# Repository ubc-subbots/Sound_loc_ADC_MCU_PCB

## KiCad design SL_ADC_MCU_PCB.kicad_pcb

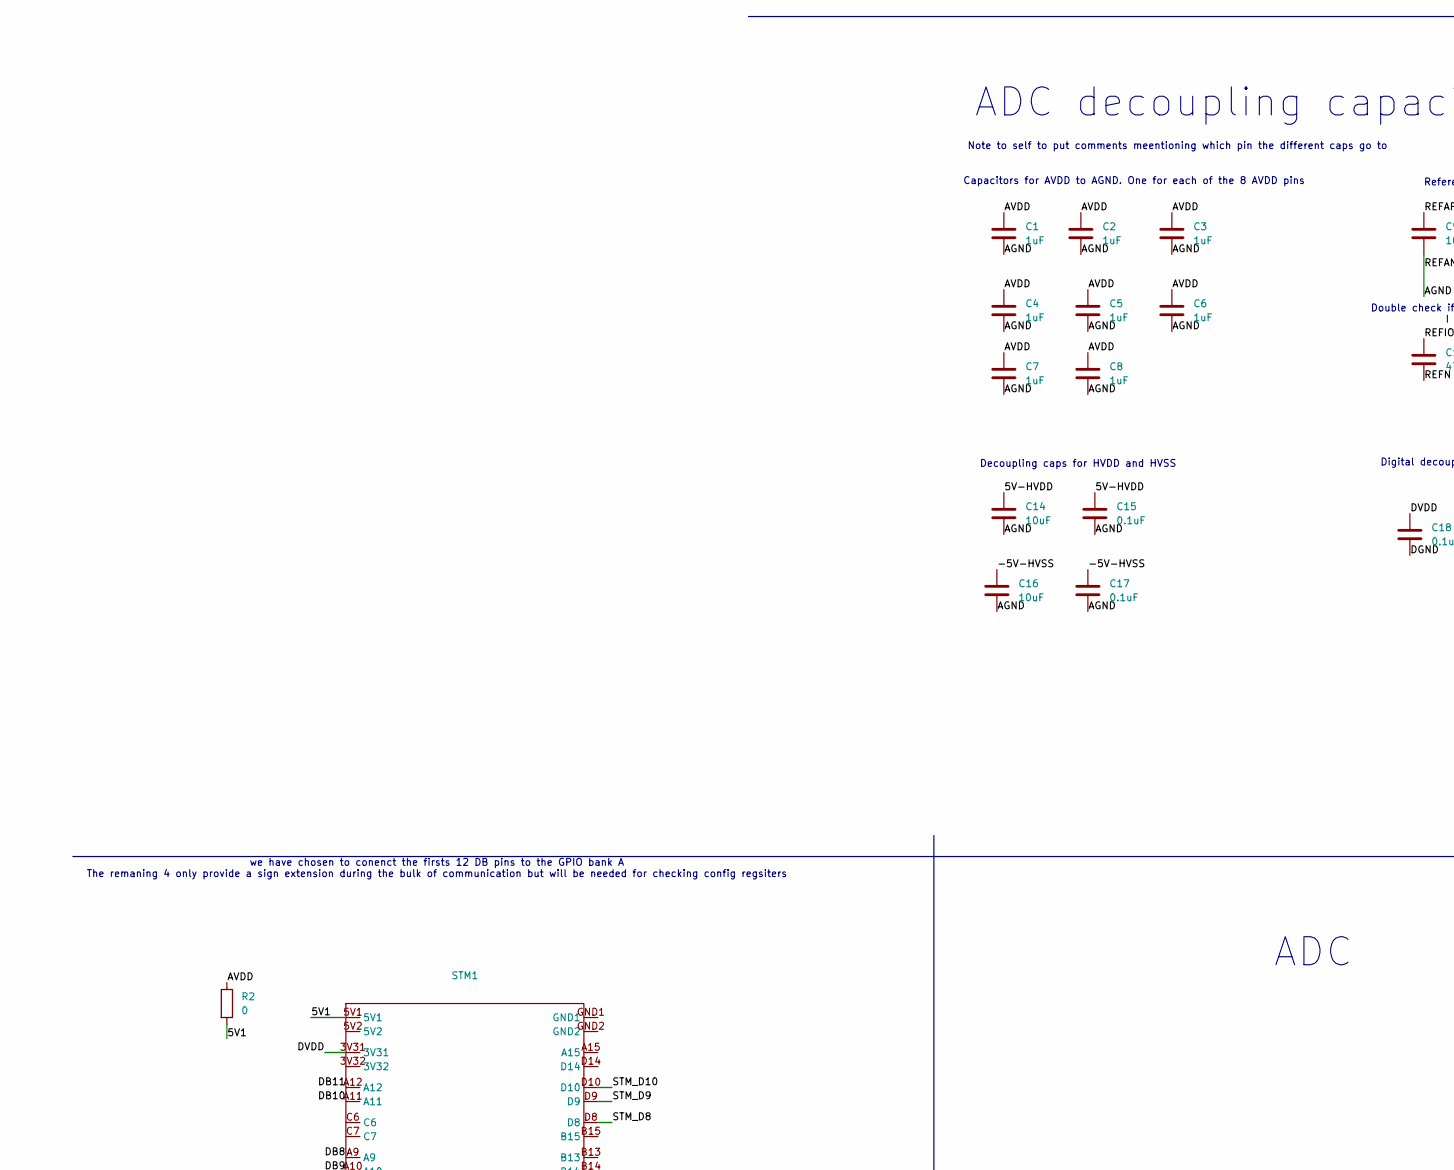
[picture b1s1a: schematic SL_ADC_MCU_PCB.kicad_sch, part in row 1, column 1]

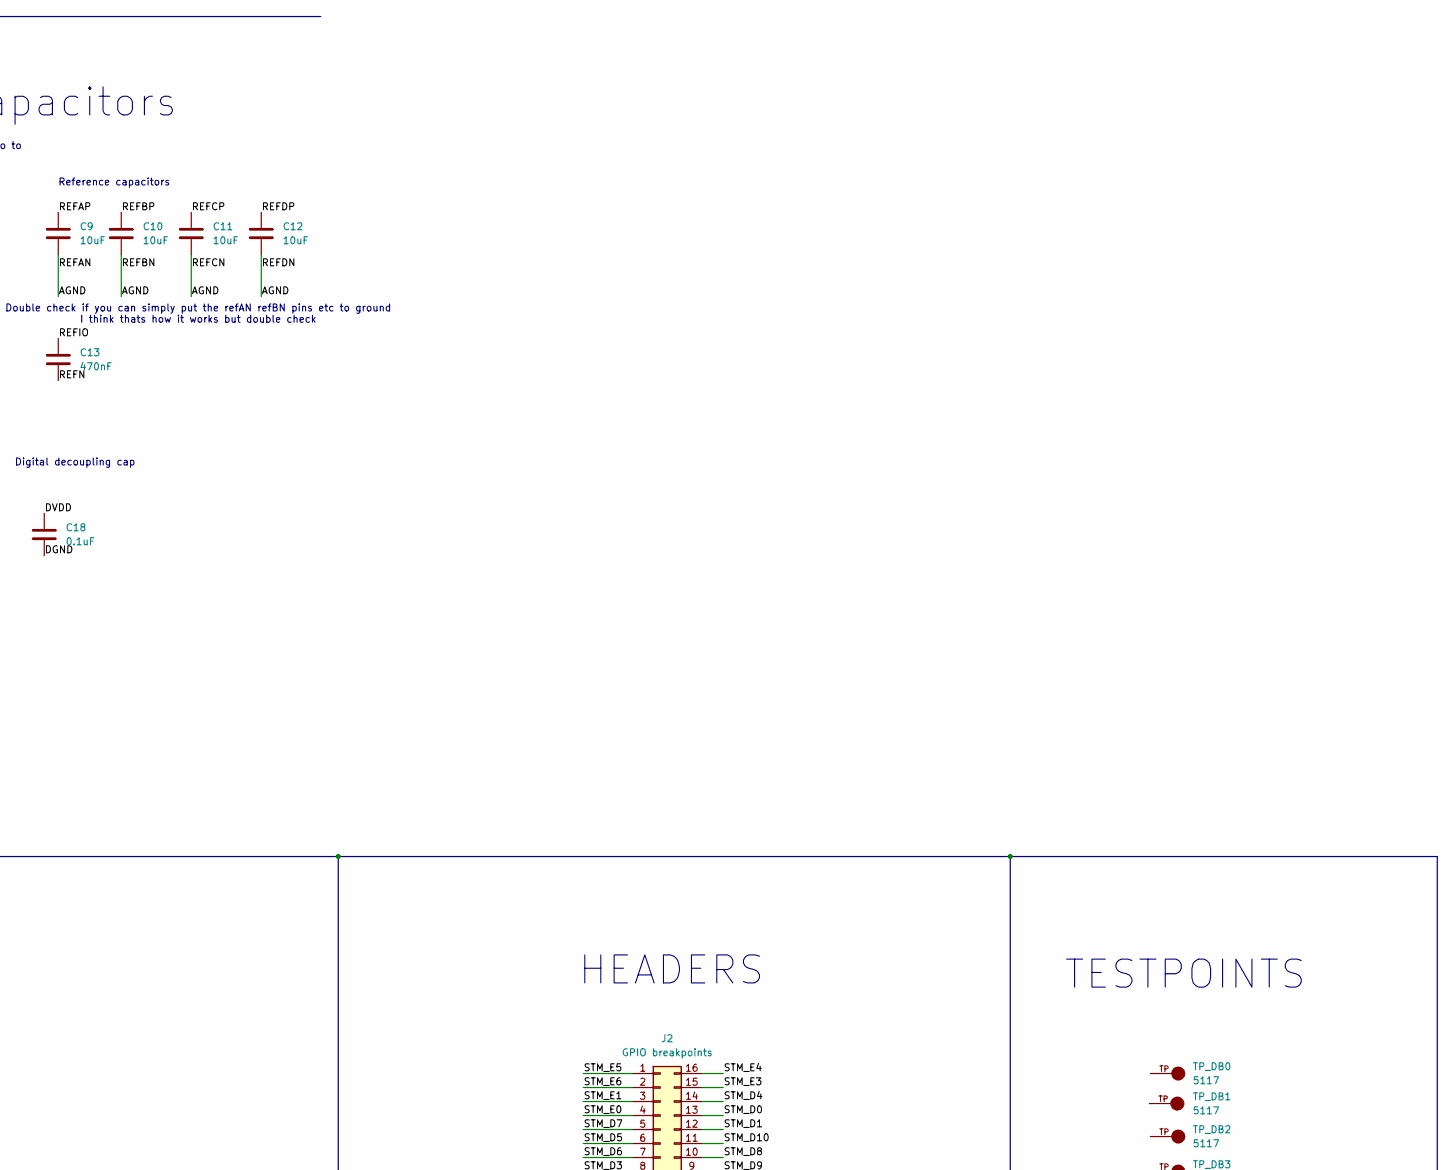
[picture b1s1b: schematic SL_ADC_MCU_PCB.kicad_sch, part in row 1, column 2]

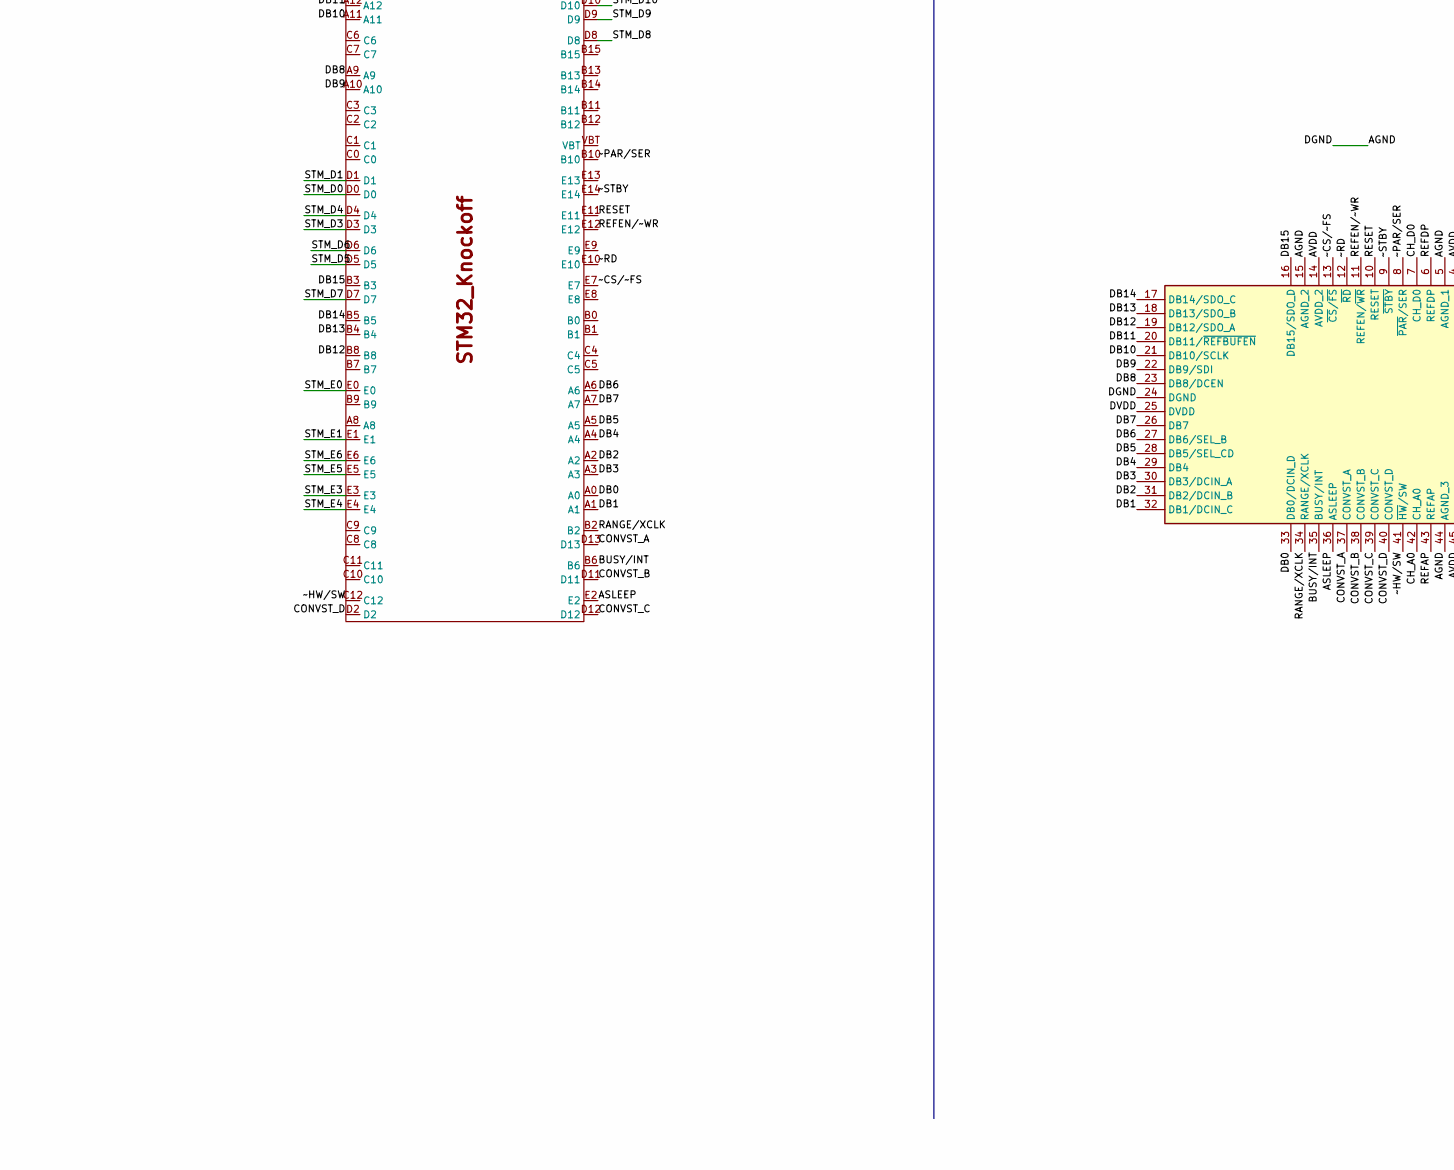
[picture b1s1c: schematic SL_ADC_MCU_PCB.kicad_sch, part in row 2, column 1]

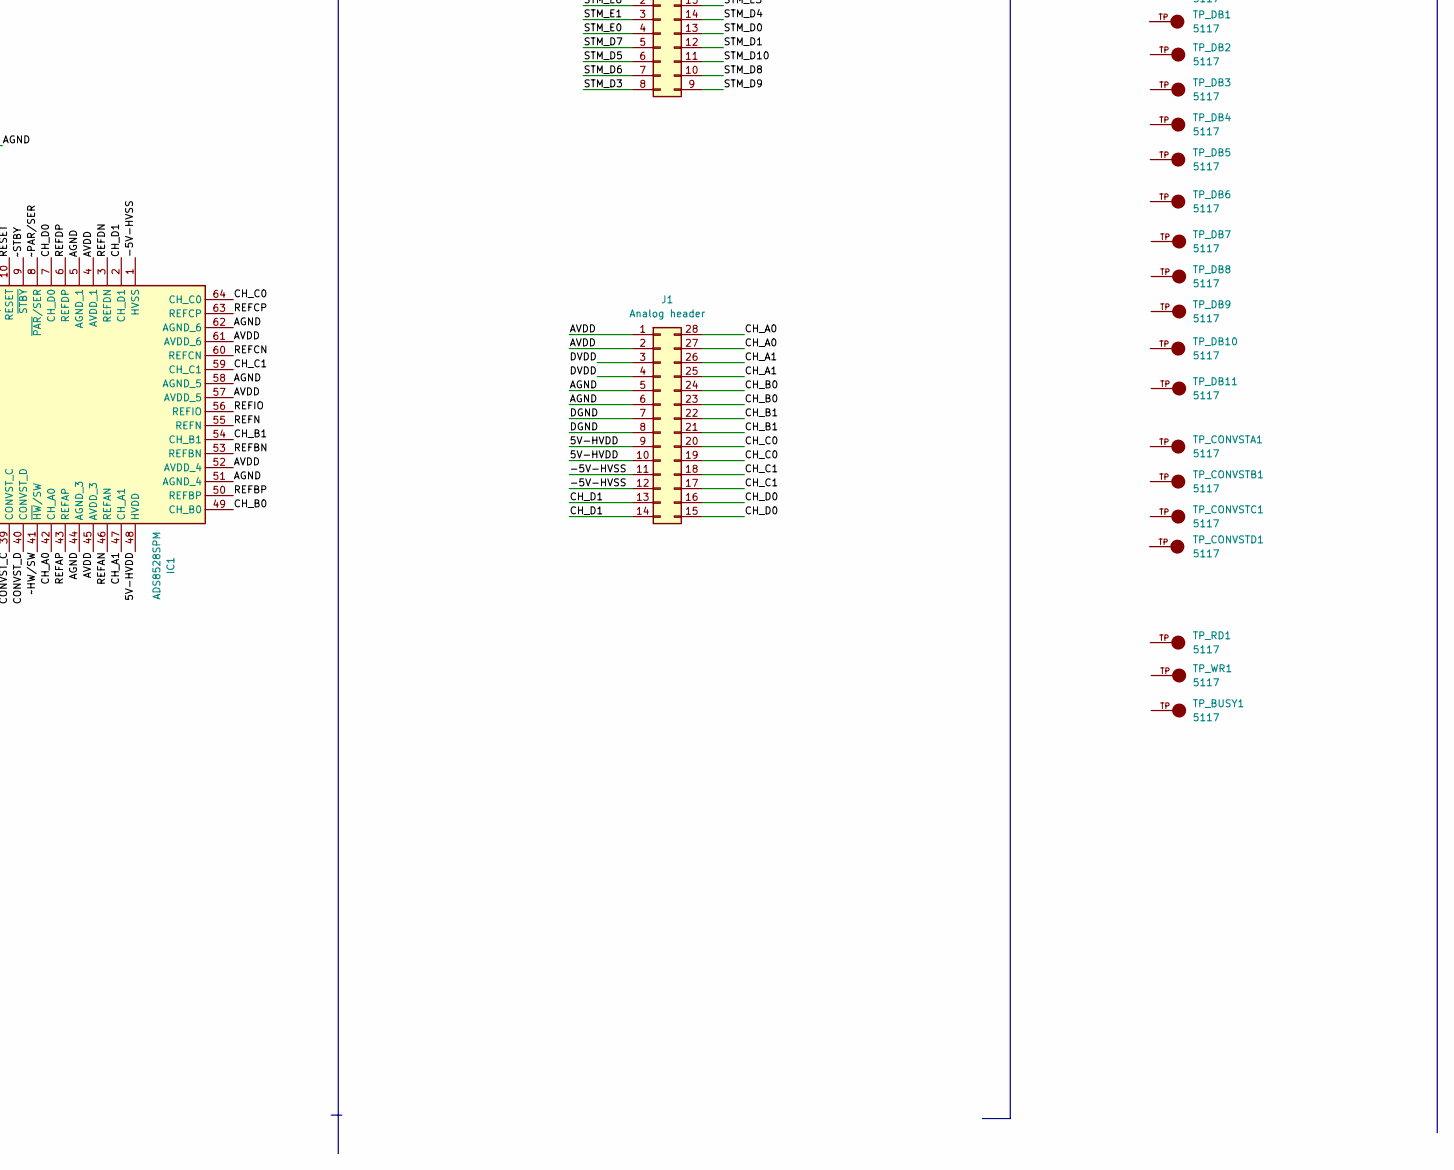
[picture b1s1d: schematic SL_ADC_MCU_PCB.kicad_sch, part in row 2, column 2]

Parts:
C1, C2, C3, C4, C5, C6, C7, C8: 1uF; C_0805_2012Metric_Pad1.18x1.45mm_HandSolder; Manufacturer_Part_Number CL21B105KBFNNNE
C9, C10, C11, C12, C14, C16: 10uF; C_0805_2012Metric_Pad1.18x1.45mm_HandSolder; Manufacturer_Part_Number CL21B106KOQNNNE
C13: 470nF; C_0805_2012Metric_Pad1.18x1.45mm_HandSolder; Manufacturer_Part_Number C0805C474K5RECTU
C15, C17, C18: 0.1uF; C_0805_2012Metric_Pad1.18x1.45mm_HandSolder; Manufacturer_Part_Number CL21B104KBCNNNC
IC1: ADS8528SPM; QFP50P1200X1200X160-64N; Manufacturer_Part_Number ADS8528SPM; Mouser Part Number 595-ADS8528SPM
J1: Analog header; PinHeader_2x14_P2.54mm_Vertical
J2: GPIO breakpoints; PinHeader_2x08_P2.54mm_Vertical
R2: 0; R_0805_2012Metric_Pad1.20x1.40mm_HandSolder; Manufacturer_Part_Number RC0805JR-070RL
STM1: STM32H7_knockoff
TP_BUSY1: 5117; KEYSTONE_5117; PARTREV H
TP_CONVSTA1: 5117; KEYSTONE_5117; PARTREV H
TP_CONVSTB1: 5117; KEYSTONE_5117; PARTREV H
TP_CONVSTC1: 5117; KEYSTONE_5117; PARTREV H
TP_CONVSTD1: 5117; KEYSTONE_5117; PARTREV H
TP_DB0, TP_DB1, TP_DB2, TP_DB3, TP_DB4, TP_DB5, TP_DB6, TP_DB7, TP_DB8, TP_DB9, TP_DB10, TP_DB11: 5117; KEYSTONE_5117; PARTREV H
TP_RD1: 5117; KEYSTONE_5117; PARTREV H
TP_WR1: 5117; KEYSTONE_5117; PARTREV H

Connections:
/5V1: R2.2, STM1.5V1
/5V-HVDD: C14.1, C15.1, IC1.48 (HVDD), J1.9, J1.10
/-5V-HVSS: C16.1, C17.1, IC1.1 (HVSS), J1.11, J1.12
/AGND: C1.2, C2.2, C3.2, C4.2, C5.2, C6.2, C7.2, C8.2, C9.2, C10.2, C11.2, C12.2, C14.2, C15.2, C16.2, C17.2, C18.2, IC1.3 (REFDN), IC1.5 (AGND_1), IC1.15 (AGND_2), IC1.24 (DGND), IC1.44 (AGND_3), IC1.46 (REFAN), IC1.51 (AGND_4), IC1.53 (REFBN), IC1.58 (AGND_5), IC1.60 (REFCN), IC1.62 (AGND_6), J1.5, J1.6, J1.7, J1.8
/ASLEEP: IC1.36 (ASLEEP), STM1.E2
/AVDD: C1.1, C2.1, C3.1, C4.1, C5.1, C6.1, C7.1, C8.1, IC1.4 (AVDD_1), IC1.14 (AVDD_2), IC1.45 (AVDD_3), IC1.52 (AVDD_4), IC1.57 (AVDD_5), IC1.61 (AVDD_6), J1.1, J1.2, R2.1
/BUSY/INT: IC1.35 (BUSY/INT), STM1.B6
/CH_A0: IC1.42 (CH_A0), J1.27, J1.28
/CH_A1: IC1.47 (CH_A1), J1.25, J1.26
/CH_B0: IC1.49 (CH_B0), J1.23, J1.24
/CH_B1: IC1.54 (CH_B1), J1.21, J1.22
/CH_C0: IC1.64 (CH_C0), J1.19, J1.20
/CH_C1: IC1.59 (CH_C1), J1.17, J1.18
/CH_D0: IC1.7 (CH_D0), J1.15, J1.16
/CH_D1: IC1.2 (CH_D1), J1.13, J1.14
/CONVST_A: IC1.37 (CONVST_A), STM1.D13
/CONVST_B: IC1.38 (CONVST_B), STM1.D11
/CONVST_C: IC1.39 (CONVST_C), STM1.D12
/CONVST_D: IC1.40 (CONVST_D), STM1.D2
/DB0: IC1.33 (DB0/DCIN_D), STM1.A0
/DB1: IC1.32 (DB1/DCIN_C), STM1.A1
/DB2: IC1.31 (DB2/DCIN_B), STM1.A2
/DB3: IC1.30 (DB3/DCIN_A), STM1.A3
/DB4: IC1.29 (DB4), STM1.A4
/DB5: IC1.28 (DB5/SEL_CD), STM1.A5
/DB6: IC1.27 (DB6/SEL_B), STM1.A6
/DB7: IC1.26 (DB7), STM1.A7
/DB8: IC1.23 (DB8/DCEN), STM1.A9
/DB9: IC1.22 (DB9/SDI), STM1.A10
/DB10: IC1.21 (DB10/SCLK), STM1.A11
/DB11: IC1.20 (DB11/~REFBUFEN), STM1.A12
/DB12: IC1.19 (DB12/SDO_A), STM1.B8
/DB13: IC1.18 (DB13/SDO_B), STM1.B4
/DB14: IC1.17 (DB14/SDO_C), STM1.B5
/DB15: IC1.16 (DB15/SDO_D), STM1.B3
/DVDD: C18.1, IC1.25 (DVDD), J1.3, J1.4, STM1.3V31
/RANGE/XCLK: IC1.34 (RANGE/XCLK), STM1.B2
/REFAP: C9.1, IC1.43 (REFAP)
/REFBP: C10.1, IC1.50 (REFBP)
/REFCP: C11.1, IC1.63 (REFCP)
/REFDP: C12.1, IC1.6 (REFDP)
/REFEN/~WR: IC1.11 (REFEN/~WR), STM1.E12
/REFIO: C13.1, IC1.56 (REFIO)
/REFN: C13.2, IC1.55 (REFN)
/RESET: IC1.10 (RESET), STM1.E11
/STM_D0: J2.13, STM1.D0
/STM_D1: J2.12, STM1.D1
/STM_D3: J2.8, STM1.D3
/STM_D4: J2.14, STM1.D4
/STM_D5: J2.6, STM1.D5
/STM_D6: J2.7, STM1.D6
/STM_D7: J2.5, STM1.D7
/STM_D8: J2.10, STM1.D8
/STM_D9: J2.9, STM1.D9
/STM_D10: J2.11, STM1.D10
/STM_E0: J2.4, STM1.E0
/STM_E1: J2.3, STM1.E1
/STM_E3: J2.15, STM1.E3
/STM_E4: J2.16, STM1.E4
/STM_E5: J2.1, STM1.E5
/STM_E6: J2.2, STM1.E6
/~CS/~FS: IC1.13 (~CS/~FS), STM1.E7
/~HW/SW: IC1.41 (~HW/SW), STM1.C12
/~PAR/SER: IC1.8 (~PAR/SER), STM1.B10
/~RD: IC1.12 (~RD), STM1.E10
/~STBY: IC1.9 (~STBY), STM1.E14

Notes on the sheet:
Decoupling caps for HVDD and HVSS
ADC decoupling capacitors
Reference capacitors
HEADERS
ADC
Digital decoupling cap
we have chosen to conenct the firsts 12 DB pins to the GPIO bank A The remaning 4 only provide a sign extension during the bulk of communication but will be needed for checking config regsiters
TESTPOINTS
Double check if you can simply put the refAN refBN pins etc to ground I think thats how it works but double check
Capacitors for AVDD to AGND. One for each of the 8 AVDD pins
Note to self to put comments meentioning which pin the different caps go to

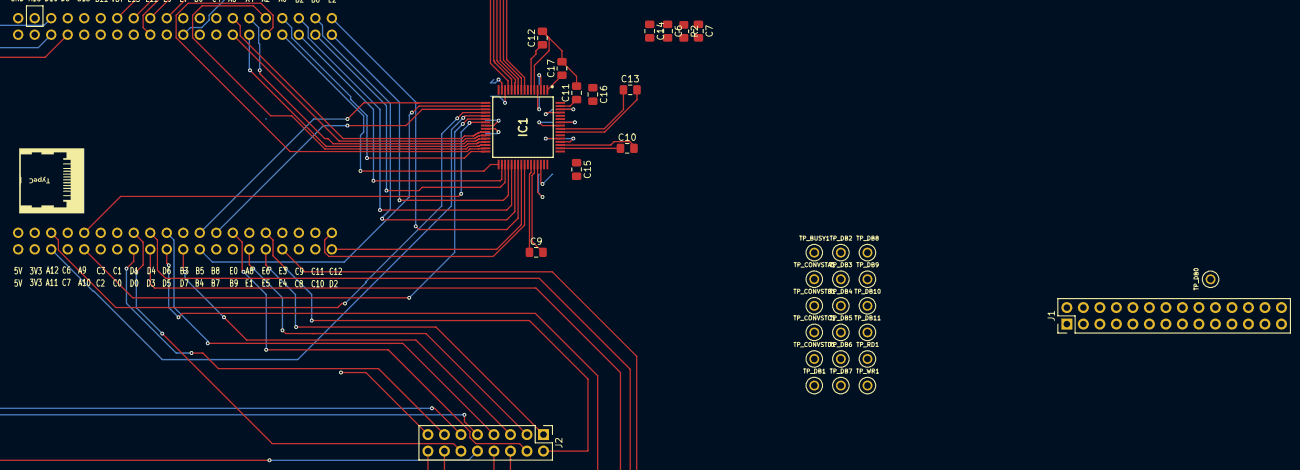
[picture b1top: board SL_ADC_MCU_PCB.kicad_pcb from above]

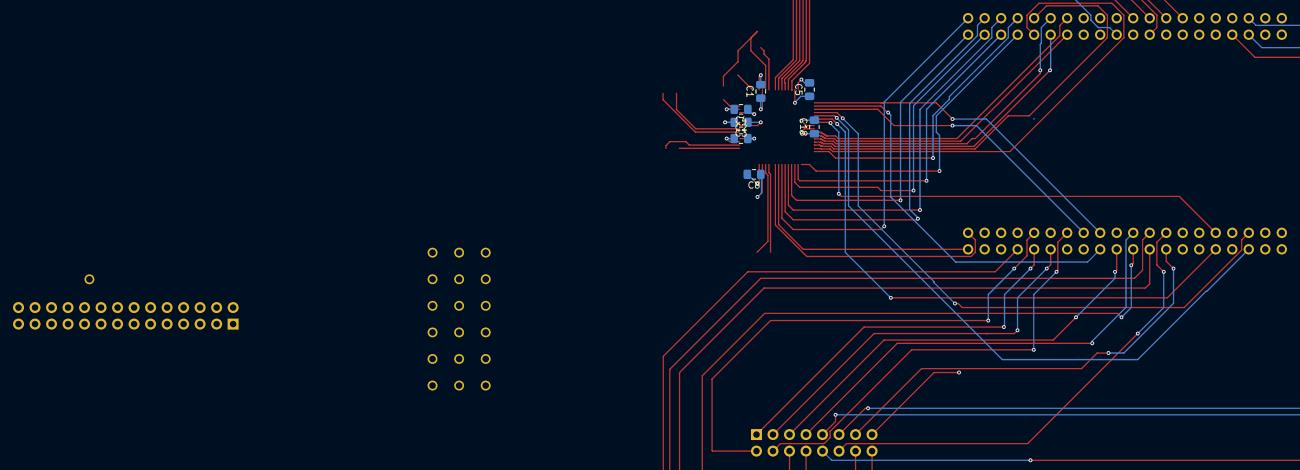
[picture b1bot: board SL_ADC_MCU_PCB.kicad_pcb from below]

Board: 2 copper layers, 42 parts (7 on the bottom side), 66 nets.

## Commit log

2026-01-10 Used offical Kicad gitignore
    https://github.com/github/gitignore/blob/main/KiCad.gitignore
2026-01-10 Made PCB project file
2026-01-10 Added ADS8528 footprint
2026-01-11 made custom model for STM32H7 sus amazon board, currently does not work but will fix
2026-01-13 added altium based schematic and footprint for the STM32 H7 dev board into additional docs
2026-01-17 changed some confusing pin labels based on manufacturer files
2026-01-17 added type C label silkscreen to STM
2026-01-17 reanmed pins on STM footprint to be unique
2026-01-17 changed pin number error in STM footprint and added net labels to the ADC
2026-01-17 pushing again in case I didnt save things
2026-01-17 added decoupling capacitors for the AVDD to AGND for the ADC
2026-01-17 made the STM32 board schematic symbol.
2026-01-17 fixing merge issue.
2026-01-18 changed one pin name error in STM symbol
2026-01-18 Decided on connection convention between STM board and ADC, ensuring DB0 to DB11 are all on GPIO bank A for simultanious acquistion and CONVST A,B,C,and D are all on the same bank to be set simultani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
2026-01-31 madded a 0 ohm resistor
2026-01-31 0-ohm resistor for mcu power and added header for power and hydrophone channels
2026-01-31 added gpoi headers
2026-02-07 made a few visual edits and added a bunch of testpoints which apparently asks to 'annotate schematic' in the PCB editor, erm...
2026-05-23 capacitors yet to route, rest done
2026-06-28 capacitors
